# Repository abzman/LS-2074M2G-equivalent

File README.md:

# LS-2074M2G-equivalent
I wanted to change the color of the LEDs...

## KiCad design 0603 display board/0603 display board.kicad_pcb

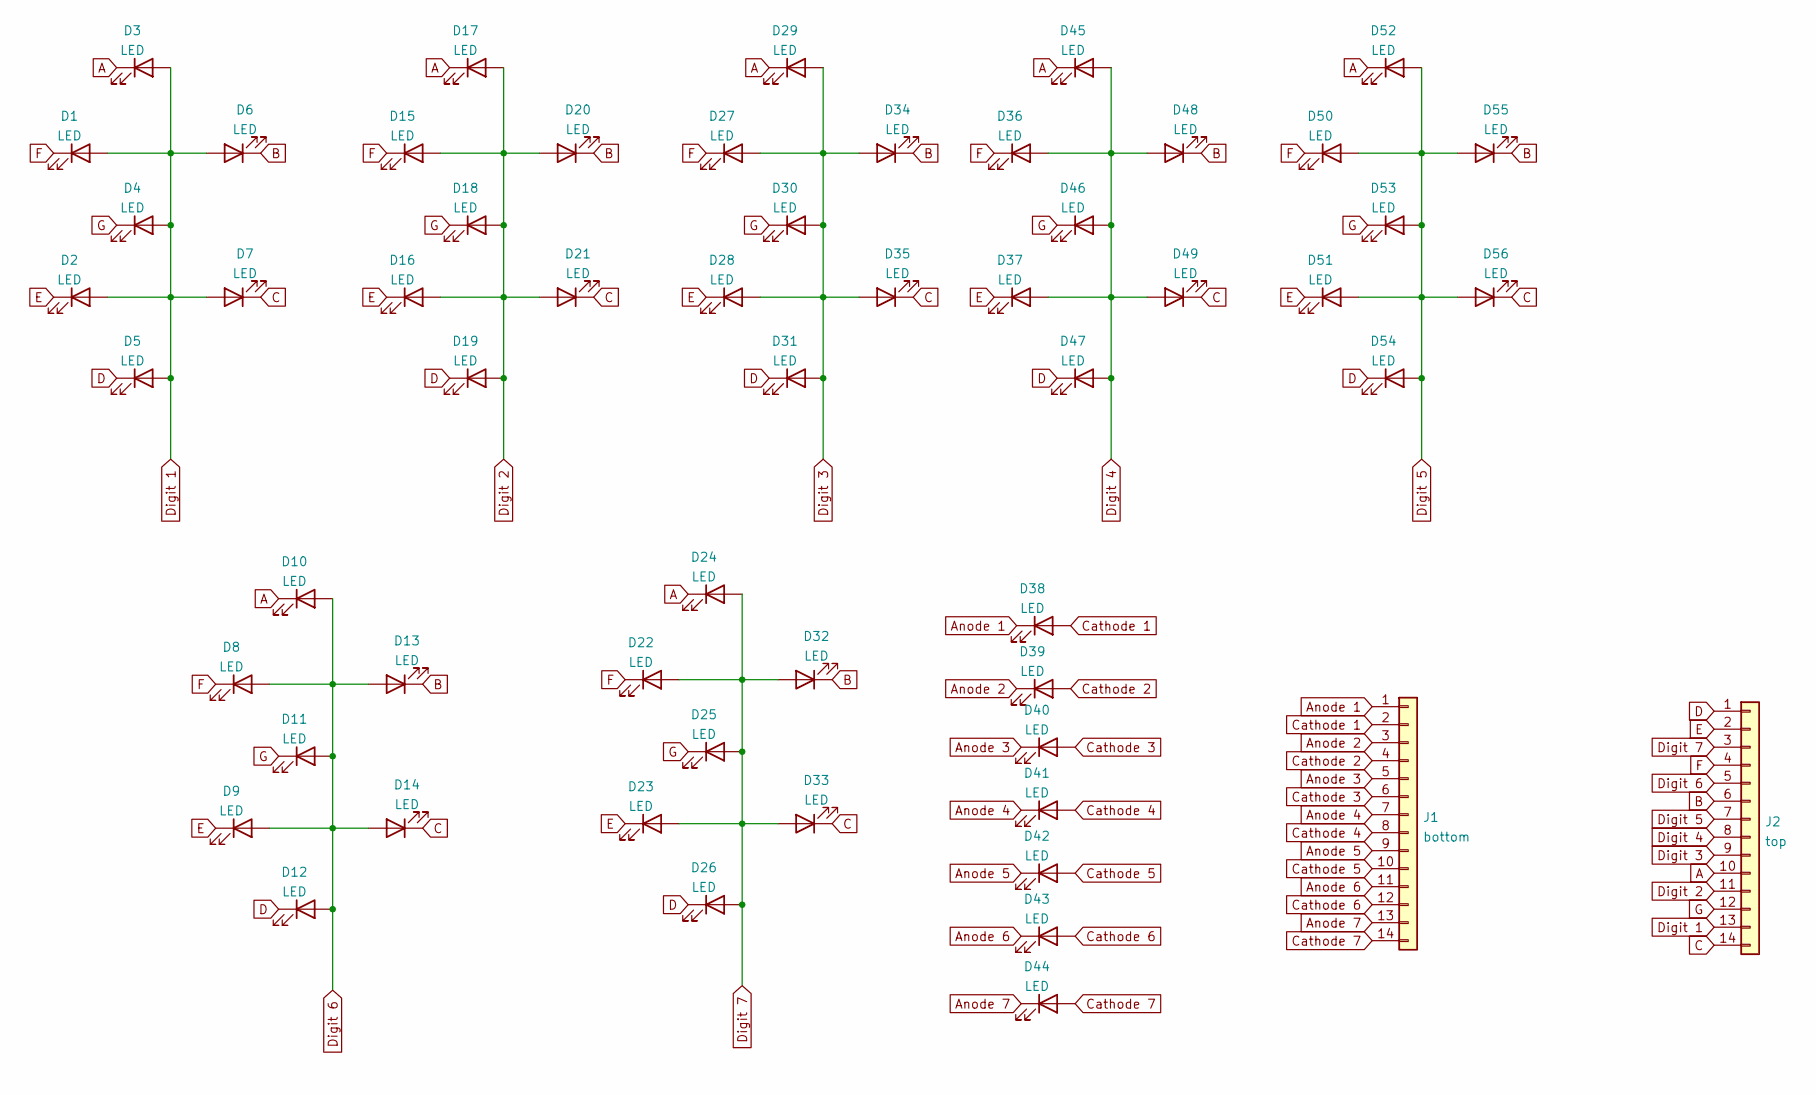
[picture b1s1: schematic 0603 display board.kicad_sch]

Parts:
D1, D2, D3, D4, D5, D6, D7, D8, D9, D10, D11, D12, D13, D14, D15, D16, D17, D18, D19, D20, D21, D22, D23, D24, D25, D26, D27, D28, D29, D30, D31, D32, D33, D34, D35, D36, D37, D38, D39, D40, D41, D42, D43, D44, D45, D46, D47, D48, D49, D50, D51, D52, D53, D54, D55, D56: LED; LED_0603_smallpads
J1: bottom; PinHeader_1x14_P2.54mm_Vertical
J2: top; PinHeader_1x14_P2.54mm_Vertical

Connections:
A: D3.1 (K), D10.1 (K), D17.1 (K), D24.1 (K), D29.1 (K), D45.1 (K), D52.1 (K), J2.10
Anode 1: D38.1 (K), J1.1
Anode 2: D39.1 (K), J1.3
Anode 3: D40.1 (K), J1.5
Anode 4: D41.1 (K), J1.7
Anode 5: D42.1 (K), J1.9
Anode 6: D43.1 (K), J1.11
Anode 7: D44.1 (K), J1.13
B: D6.1 (K), D13.1 (K), D20.1 (K), D32.1 (K), D34.1 (K), D48.1 (K), D55.1 (K), J2.6
C: D7.1 (K), D14.1 (K), D21.1 (K), D33.1 (K), D35.1 (K), D49.1 (K), D56.1 (K), J2.14
Cathode 1: D38.2 (A), J1.2
Cathode 2: D39.2 (A), J1.4
Cathode 3: D40.2 (A), J1.6
Cathode 4: D41.2 (A), J1.8
Cathode 5: D42.2 (A), J1.10
Cathode 6: D43.2 (A), J1.12
Cathode 7: D44.2 (A), J1.14
D: D5.1 (K), D12.1 (K), D19.1 (K), D26.1 (K), D31.1 (K), D47.1 (K), D54.1 (K), J2.1
Digit 1: D1.2 (A), D2.2 (A), D3.2 (A), D4.2 (A), D5.2 (A), D6.2 (A), D7.2 (A), J2.13
Digit 2: D15.2 (A), D16.2 (A), D17.2 (A), D18.2 (A), D19.2 (A), D20.2 (A), D21.2 (A), J2.11
Digit 3: D27.2 (A), D28.2 (A), D29.2 (A), D30.2 (A), D31.2 (A), D34.2 (A), D35.2 (A), J2.9
Digit 4: D36.2 (A), D37.2 (A), D45.2 (A), D46.2 (A), D47.2 (A), D48.2 (A), D49.2 (A), J2.8
Digit 5: D50.2 (A), D51.2 (A), D52.2 (A), D53.2 (A), D54.2 (A), D55.2 (A), D56.2 (A), J2.7
Digit 6: D8.2 (A), D9.2 (A), D10.2 (A), D11.2 (A), D12.2 (A), D13.2 (A), D14.2 (A), J2.5
Digit 7: D22.2 (A), D23.2 (A), D24.2 (A), D25.2 (A), D26.2 (A), D32.2 (A), D33.2 (A), J2.3
E: D2.1 (K), D9.1 (K), D16.1 (K), D23.1 (K), D28.1 (K), D37.1 (K), D51.1 (K), J2.2
F: D1.1 (K), D8.1 (K), D15.1 (K), D22.1 (K), D27.1 (K), D36.1 (K), D50.1 (K), J2.4
G: D4.1 (K), D11.1 (K), D18.1 (K), D25.1 (K), D30.1 (K), D46.1 (K), D53.1 (K), J2.12

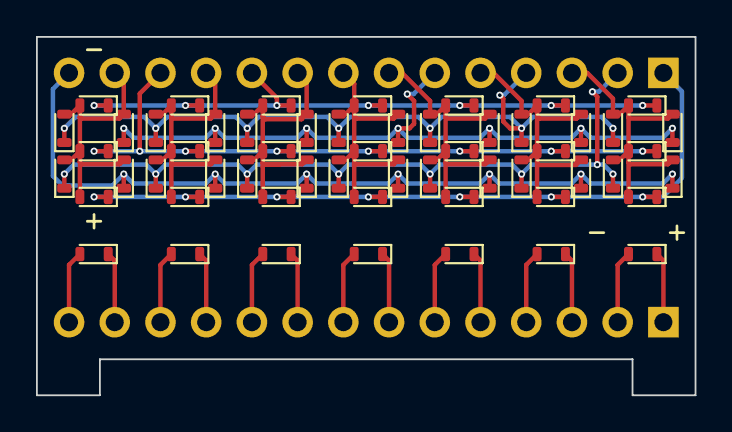
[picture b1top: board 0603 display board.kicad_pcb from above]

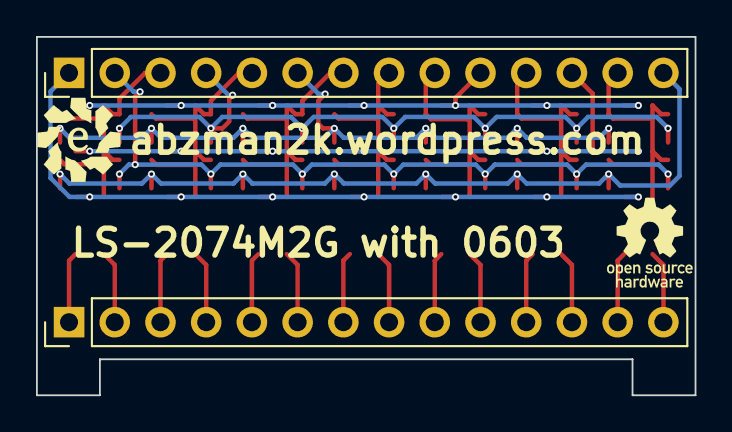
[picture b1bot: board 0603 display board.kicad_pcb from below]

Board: 2 copper layers, 36.6 x 19.9 mm, 58 parts (2 on the bottom side), 28 nets.

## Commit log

2022-10-23 schematic done
2022-10-23 finished first layout
2022-10-23 smaller footprint
2022-11-25 generated gerbers
